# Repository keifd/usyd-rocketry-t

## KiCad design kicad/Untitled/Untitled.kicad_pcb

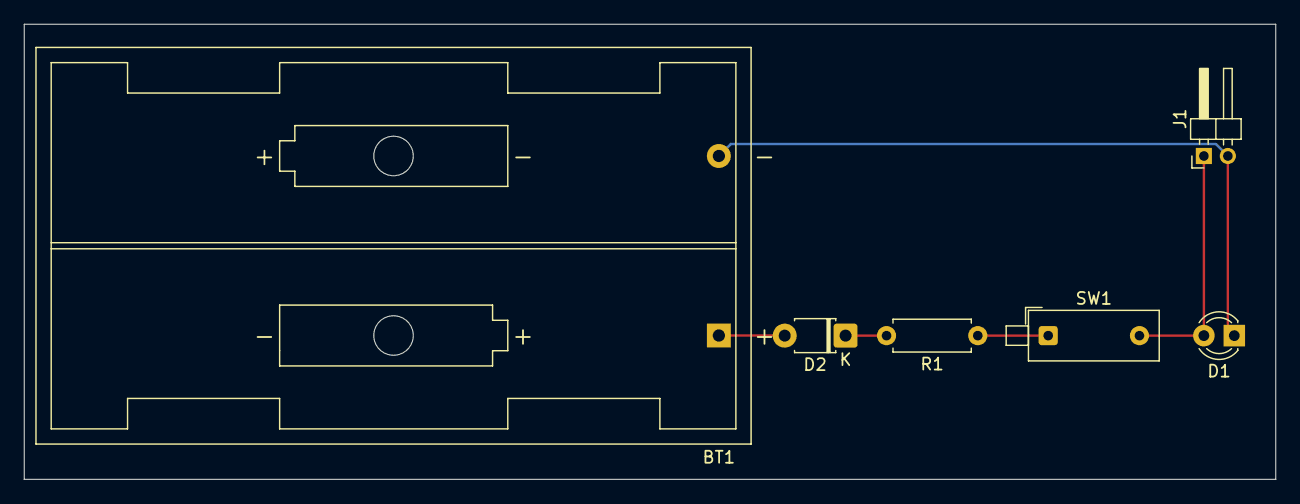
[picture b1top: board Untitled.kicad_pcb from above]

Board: 2 copper layers, 104.5 x 38.0 mm, 6 parts (0 on the bottom side), 5 nets.

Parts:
BT1: Battery; BatteryHolder_Keystone_2462_2xAA
D1: LED; LED_D3.0mm
D2: D_Small; D_T-1_P5.08mm_Horizontal
J1: Conn_01x02; PinHeader_1x02_P2.00mm_Horizontal
R1: R; R_Axial_DIN0207_L6.3mm_D2.5mm_P7.62mm_Horizontal
SW1: SW_Push; SW_DIP_SPSTx01_Piano_10.8x4.1mm_W7.62mm_P2.54mm

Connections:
unnamed: BT1.1 (+), D2.2 (A)
unnamed: BT1.2 (-), D1.1 (K), J1.2
unnamed: D1.2 (A), J1.1, SW1.2
unnamed: D2.1 (K), R1.2
unnamed: R1.1, SW1.1

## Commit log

2025-09-10 codingtask
